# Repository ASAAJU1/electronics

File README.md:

Initial Conversion from the SVN Repo at:
http://code.google.com/p/jctc-electronics/

Most board and lbr files were made with eagle 5.x.
New designs will use Eagle 6.3 and up.

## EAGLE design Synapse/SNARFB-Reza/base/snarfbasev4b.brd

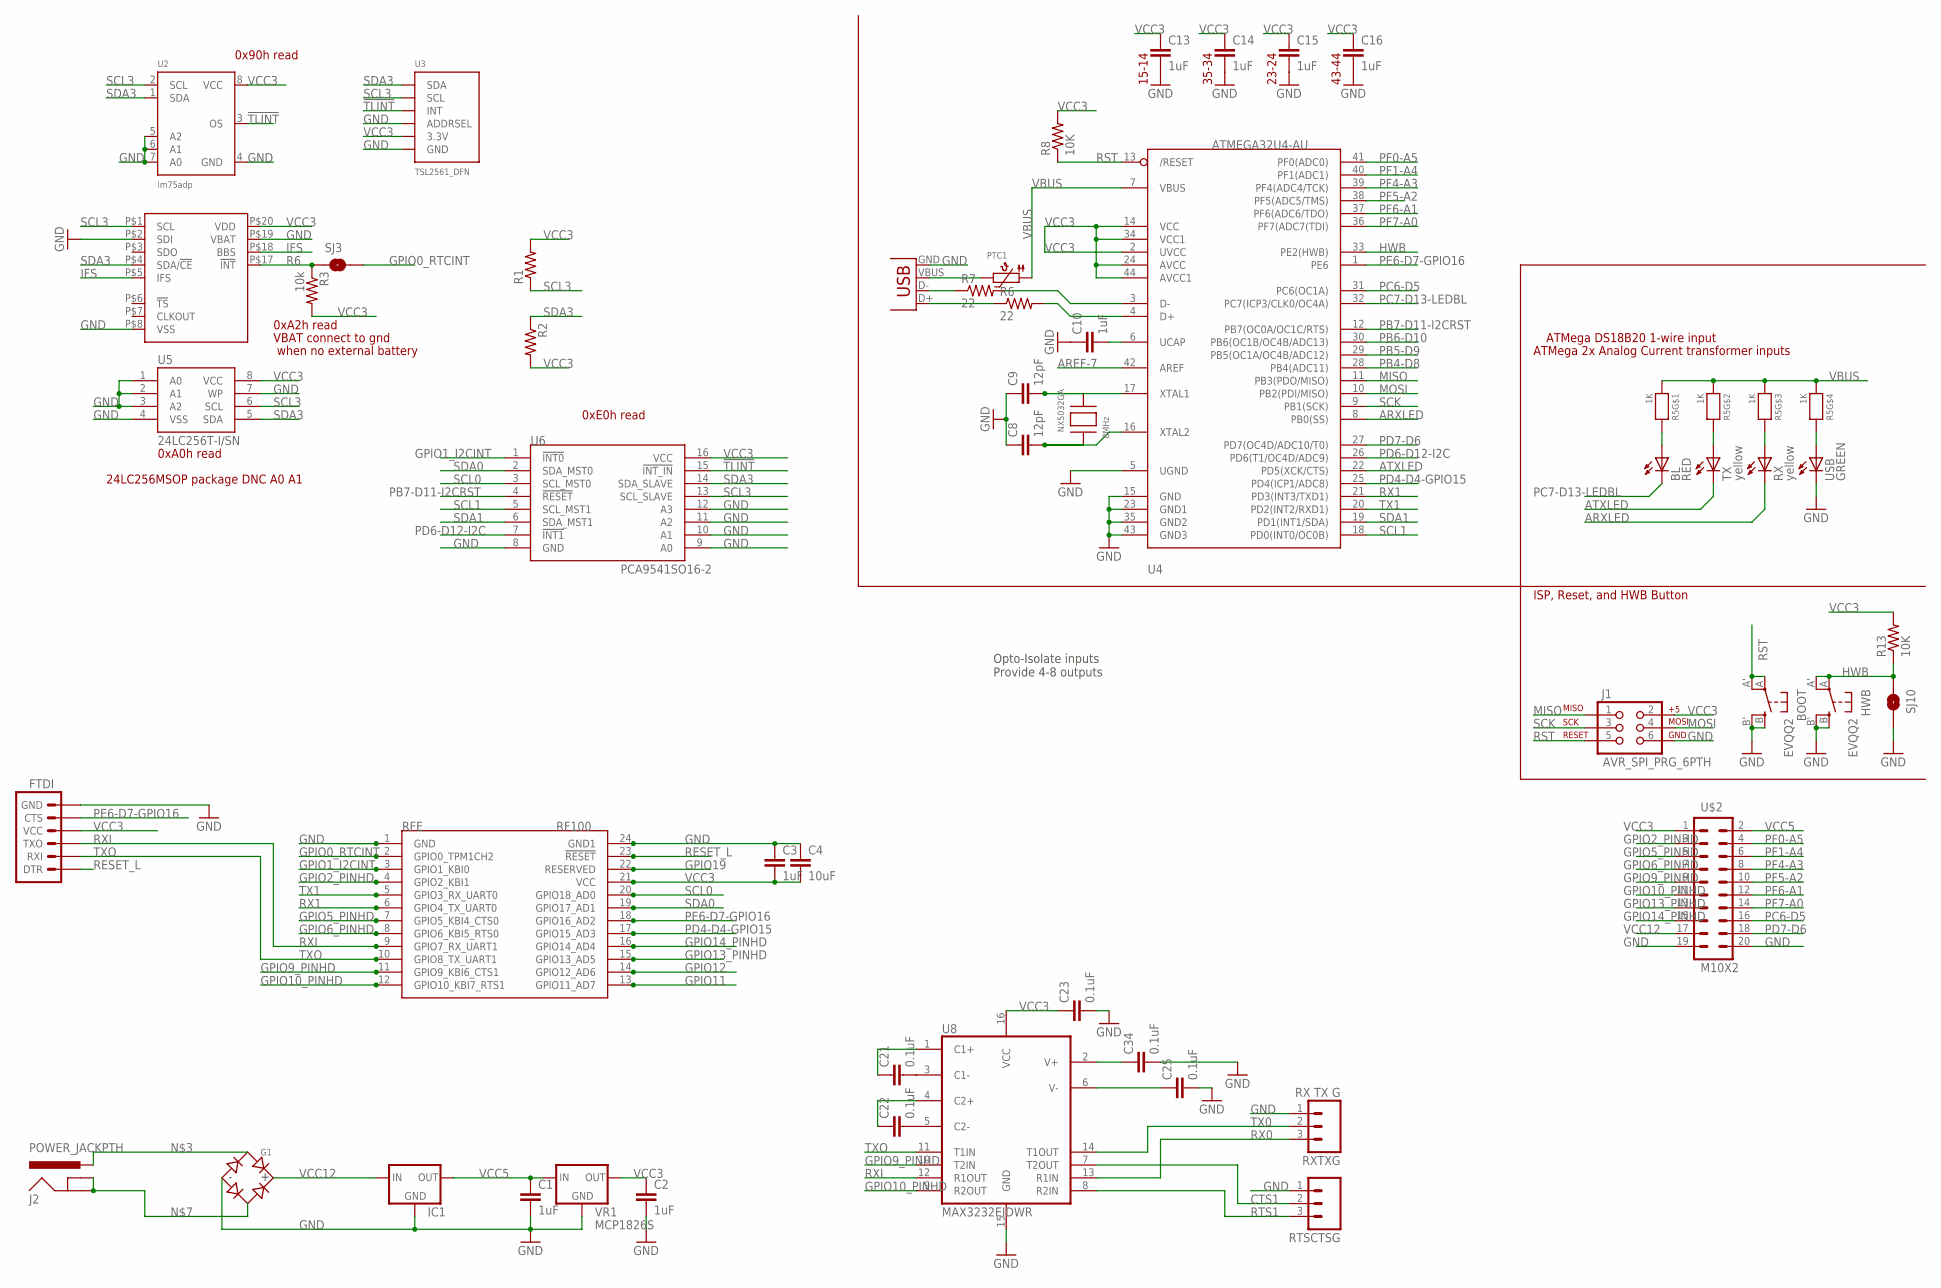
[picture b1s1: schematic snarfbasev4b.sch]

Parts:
BL: RED; LED-0603
BOOT: EVQQ2; EVQ-Q2
C1, C2, C3, C10, C13, C14, C15, C16: 1uF; 0805
C4: 10uF; 0805
C8, C9: 12pF; 0603-CAP
C21, C22, C23, C25, C34: 0.1uF; 0805
FTDI: ARDUINO_SERIAL_PROGRAMPTH; 1X06
G1: BRIDGERECTIFIER; SOIC-4
HWB: EVQQ2; EVQ-Q2
IC1: V_REG_78XXMURATA; TO220-MURATA
J1: AVR_SPI_PRG_6PTH; 2X3
J2: POWER_JACKPTH; POWER_JACK_PTH
NX5032GA: 8MHz; NX5032
PTC1: PTC1206; 1206
R1, R2: RESISTOR0805-RES; 0805
R3: 10k; 0805
R5: 1K; RESPACK_4X0603
R6, R7: 22; 0603-RES
R8, R13: 10K; 0805
RFE: RFE; SYNAPSERFENGINE-THM-SMT-JACK2
RTSCTSG: M03PTH; 1X03
RX: yellow; LED-0603
RXTXG: RX TX G; 1X03
SJ3: SOLDERJUMPERNC2; SJ_2S-NOTRACE
SJ10: HWB; SJ_2S-NO
TX: yellow; LED-0603
U1: PCF2129ASO20; SO20W
U2: lm75adp; TSSOP8
U3: TSL2561_DFN; TSL2561_FN
U4: ATMEGA32U4-AU; TQFP44
U5: 24LC256T-I/SN; SO08
U6: PCA9541SO16-2; SOIC16
U8: MAX3232EIDWR; SO016
U$2: M10X2; 2X10
USB: GREEN; LED-0603
VR1: MCP1826S; SOT223
X1: USBSMD; USB-MINIB

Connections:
!TLINT: U2.3 (OS), U3.INT, U6.15 (!INT_IN)
AREF-7: U4.42 (AREF)
ARXLED: RX.C, U4.8 (PB0(SS))
ATXLED: TX.C, U4.22 (PD5(XCK/CTS))
CTS1: RTSCTSG.2, U8.7 (T2OUT)
GND: BOOT.B (S), BOOT.B' (S1), C1.2, C2.2, C3.1, C4.1, C8.1, C9.1, C10.1, C13.2, C14.2, C15.2, C16.2, C23.2, C25.2, C34.2, FTDI.6 (GND), G1.-, HWB.B (S), HWB.B' (S1), IC1.GND, J1.6, RFE.1 (GND), RFE.24 (GND1), RFE.P1, RFE.P24, RFE.P201, RFE.P224, RTSCTSG.1, RXTXG.1, SJ10.2, U1.P$2 (SDI), U1.P$8 (VSS), U1.P$19 (VBAT), U2.4 (GND), U2.5 (A2), U2.6 (A1), U2.7 (A0), U3.ADR (ADDRSEL), U3.VSS (GND), U4.5 (UGND), U4.15 (GND), U4.23 (GND1), U4.35 (GND2), U4.43 (GND3), U5.1 (A0), U5.2 (A1), U5.3 (A2), U5.4 (VSS), U5.7 (WP), U6.8 (GND), U6.9 (A0), U6.10 (A1), U6.11 (A2), U6.12 (A3), U8.15 (GND), U$2.19, U$2.20, USB.C, VR1.2 (GND), VR1.4 (GND), X1.GND
GPIO0_RTCINT: RFE.2 (GPIO0_TPM1CH2), RFE.P2, RFE.P202, SJ3.2
GPIO1_I2CINT: RFE.3 (GPIO1_KBI0), RFE.P3, RFE.P203, U6.1 (!INT0)
GPIO2_PINHD: RFE.4 (GPIO2_KBI1), RFE.P4, RFE.P204, U$2.3
GPIO5_PINHD: RFE.7 (GPIO5_KBI4_CTS0), RFE.P7, RFE.P207, U$2.5
GPIO6_PINHD: RFE.8 (GPIO6_KBI5_RTS0), RFE.P8, RFE.P208, U$2.7
GPIO9_PINHD: RFE.11 (GPIO9_KBI6_CTS1), RFE.P11, RFE.P211, U8.10 (T2IN), U$2.9
GPIO10_PINHD: RFE.12 (GPIO10_KBI7_RTS1), RFE.P12, RFE.P212, U8.9 (R2OUT), U$2.11
GPIO11: RFE.13 (GPIO11_AD7), RFE.P13, RFE.P213
GPIO12: RFE.14 (GPIO12_AD6), RFE.P14, RFE.P214
GPIO13_PINHD: RFE.15 (GPIO13_AD5), RFE.P15, RFE.P215, U$2.13
GPIO14_PINHD: RFE.16 (GPIO14_AD4), RFE.P16, RFE.P216, U$2.15
GPIO19: RFE.22 (RESERVED), RFE.P22, RFE.P222
HWB: HWB.A, HWB.A' (P1), R13.1, SJ10.1, U4.33 (PE2(HWB))
IFS: U1.P$5 (IFS), U1.P$18 (BBS)
MISO: J1.1, U4.11 (PB3(PDO/MISO))
MOSI: J1.4, U4.10 (PB2(PDI/MISO))
unnamed: G1.~1 (AC1), J2.PWR
unnamed: C10.2, U4.6 (UCAP)
unnamed: BL.A, R5.8 (2)
unnamed: G1.~2 (AC2), J2.GND, J2.GNDBREAK
unnamed: R5.7 (2), TX.A
unnamed: R5.6 (2), RX.A
unnamed: R5.5 (2), USB.A
unnamed: C21.2, U8.3 (C1-)
unnamed: C22.2, U8.5 (C2-)
unnamed: C34.1, U8.2 (V+)
unnamed: C25.1, U8.6 (V-)
unnamed: C21.1, U8.1 (C1+)
unnamed: C22.1, U8.4 (C2+)
PB4-D8: U4.28 (PB4(ADC11))
PB5-D9: U4.29 (PB5(OC1A/OC4B/ADC12))
PB6-D10: U4.30 (PB6(OC1B/OC4B/ADC13))
PB7-D11-I2CRST: U4.12 (PB7(OC0A/OC1C/RTS)), U6.4 (!RESET)
PC6-D5: U4.31 (PC6(OC1A)), U$2.16
PC7-D13-LEDBL: BL.C, U4.32 (PC7(ICP3/CLK0/OC4A))
PD4-D4-GPIO15: RFE.17 (GPIO15_AD3), RFE.P17, RFE.P217, U4.25 (PD4(ICP1/ADC8))
PD6-D12-I2C: U4.26 (PD6(T1/OC4D/ADC9)), U6.7 (!INT1)
PD7-D6: U4.27 (PD7(OC4D/ADC10/T0)), U$2.18
PE6-D7-GPIO16: FTDI.5 (CTS), RFE.18 (GPIO16_AD2), RFE.P18, RFE.P218, U4.1 (PE6)
PF0-A5: U4.41 (PF0(ADC0)), U$2.4
PF1-A4: U4.40 (PF1(ADC1)), U$2.6
PF4-A3: U4.39 (PF4(ADC4/TCK)), U$2.8
PF5-A2: U4.38 (PF5(ADC5/TMS)), U$2.10
PF6-A1: U4.37 (PF6(ADC6/TDO)), U$2.12
PF7-A0: U4.36 (PF7(ADC7(TDI)), U$2.14
R6: R3.1, SJ3.1, U1.P$17 (!INT)
RESET_L: FTDI.1 (DTR), RFE.23 (!RESET), RFE.P23, RFE.P223
RST: BOOT.A, BOOT.A' (P1), J1.5, R8.1, U4.13 (/RESET)
RTS1: RTSCTSG.3, U8.8 (R2IN)
RX0: RXTXG.3, U8.13 (R1IN)
RX1: RFE.6 (GPIO4_TX_UART0), RFE.P6, RFE.P206, U4.21 (PD3(INT3/TXD1))
RXI: FTDI.3 (TXO), RFE.9 (GPIO7_RX_UART1), RFE.P9, RFE.P209, U8.12 (R1OUT)
SCK: J1.3, U4.9 (PB1(SCK))
SCL0: RFE.20 (GPIO18_AD0), RFE.P20, RFE.P220, U6.3 (SCL_MST0)
SCL1: U4.18 (PD0(INT0/OC0B)), U6.5 (SCL_MST1)
SCL3: R1.1, U1.P$1 (SCL), U2.2 (SCL), U3.CLK (SCL), U5.6 (SCL), U6.13 (SCL_SLAVE)
SDA0: RFE.19 (GPIO17_AD1), RFE.P19, RFE.P219, U6.2 (SDA_MST0)
SDA1: U4.19 (PD1(INT1/SDA)), U6.6 (SDA_MST1)
SDA3: R2.1, U1.P$4 (SDA/!CE), U2.1 (SDA), U3.DATA (SDA), U5.5 (SDA), U6.14 (SDA_SLAVE)
TX0: RXTXG.2, U8.14 (T1OUT)
TX1: RFE.5 (GPIO3_RX_UART0), RFE.P5, RFE.P205, U4.20 (PD2(INT2/RXD1))
TXO: FTDI.2 (RXI), RFE.10 (GPIO8_TX_UART1), RFE.P10, RFE.P210, U8.11 (T1IN)
UDM_N: R7.1, X1.D-
UDM_P: R6.1, X1.D+
UD_N: R7.2, U4.3 (D-)
UD_P: R6.2, U4.4 (D+)
VBUS: PTC1.1, R5.1, R5.2 (1), R5.3 (1), R5.4 (1), U4.7 (VBUS)
VBUSRAW: PTC1.2, X1.VBUS
VCC3: C2.1, C3.2, C4.2, C13.1, C14.1, C15.1, C16.1, C23.1, FTDI.4 (VCC), J1.2, R1.2, R2.2, R3.2, R8.2, R13.2, RFE.21 (VCC), RFE.P21, RFE.P221, U1.P$20 (VDD), U2.8 (VCC), U3.VDD (3.3V), U4.2 (UVCC), U4.14 (VCC), U4.24 (AVCC), U4.34 (VCC1), U4.44 (AVCC1), U5.8 (VCC), U6.16 (VCC), U8.16 (VCC), U$2.1, VR1.3 (OUT)
VCC5: C1.1, IC1.OUT, U$2.2, VR1.1 (IN)
VCC12: G1.+, IC1.IN, U$2.17
XTAL_N: C9.2, NX5032GA.P$2, U4.17 (XTAL1)
XTAL_P: C8.2, NX5032GA.P$1, U4.16 (XTAL2)

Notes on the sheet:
24LC256MSOP package DNC A0 A1
0xA2h read
0xA0h read
0x90h read
VBAT connect to gnd
when no external battery
43-44
35-34
23-24
15-14
Opto-Isolate inputs Provide 4-8 outputs
ISP, Reset, and HWB Button
ATMega DS18B20 1-wire input
ATMega 2x Analog Current transformer inputs
0xE0h read

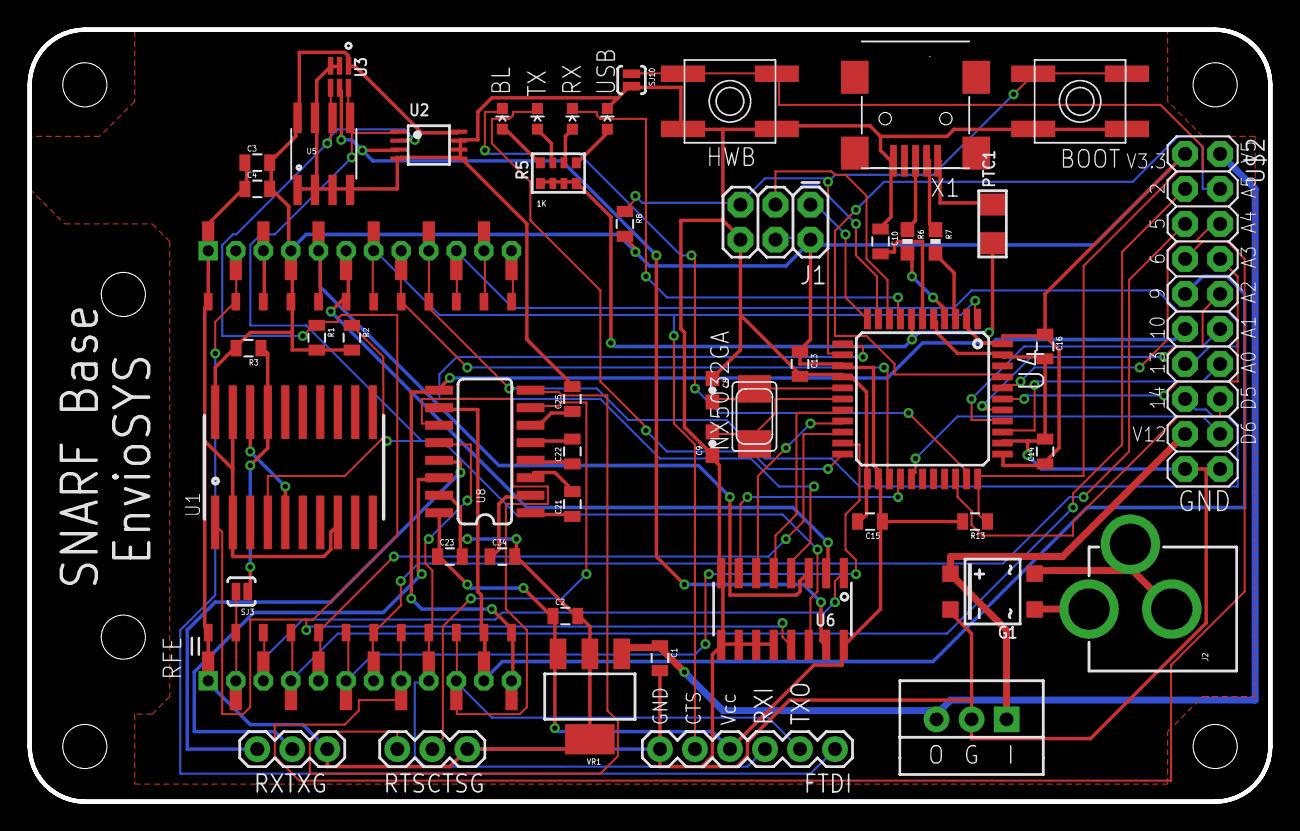
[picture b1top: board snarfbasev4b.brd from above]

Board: 2 copper layers, 90.0 x 56.0 mm, 54 parts (1 on the bottom side), 75 nets.

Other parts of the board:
U$1: ENVIOSYS_LOGO2
U$3: DP9056_V1

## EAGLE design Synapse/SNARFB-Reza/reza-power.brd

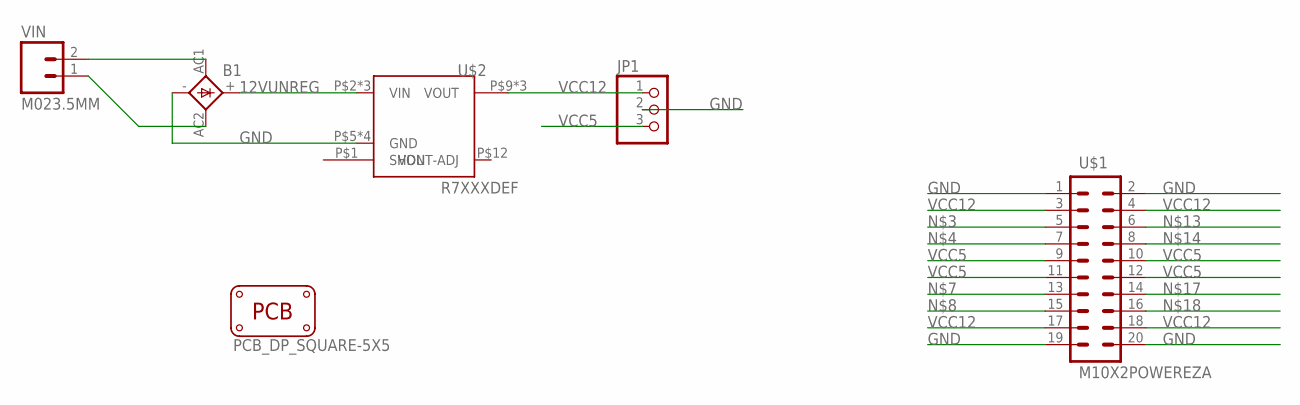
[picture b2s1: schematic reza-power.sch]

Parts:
B1: 1KAB
JP1: PINHD-1X3CB; 1X03-CLEANBIG
PCB1: PCB_DP_SQUARE-5X5; DP5050_V1
U$1: M10X2POWEREZA; REZAPOWER_INTERBOARD
U$2: R7XXXDEF; 1X12_RECOM
VIN: M023.5MM; SCREWTERMINAL-3.5MM-2

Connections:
12VUNREG: B1.+, U$2.P$2 (VIN), U$2.P$3 (VIN), U$2.P$4 (VIN)
24VAC1: B1.AC2, VIN.1
24VAC2: B1.AC1, VIN.2
GND: B1.-, JP1.2, U$1.1, U$1.2, U$1.19, U$1.20, U$2.P$5 (GND), U$2.P$6 (GND), U$2.P$7 (GND), U$2.P$8 (GND)
VCC5: JP1.3, U$1.9, U$1.10, U$1.11, U$1.12
VCC12: JP1.1, U$1.3, U$1.4, U$1.17, U$1.18, U$2.P$9 (VOUT), U$2.P$10 (VOUT), U$2.P$11 (VOUT)

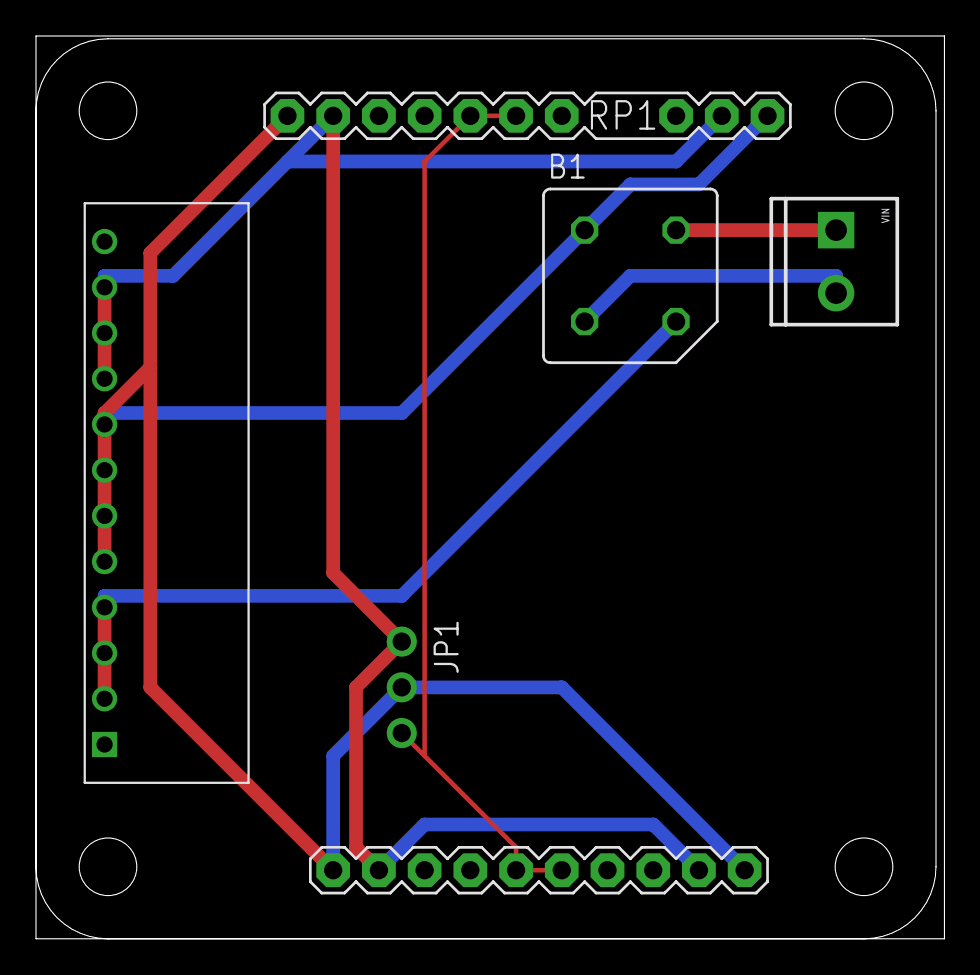
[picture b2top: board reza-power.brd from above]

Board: 2 copper layers, 50.5 x 50.2 mm, 6 parts (0 on the bottom side), 6 nets.

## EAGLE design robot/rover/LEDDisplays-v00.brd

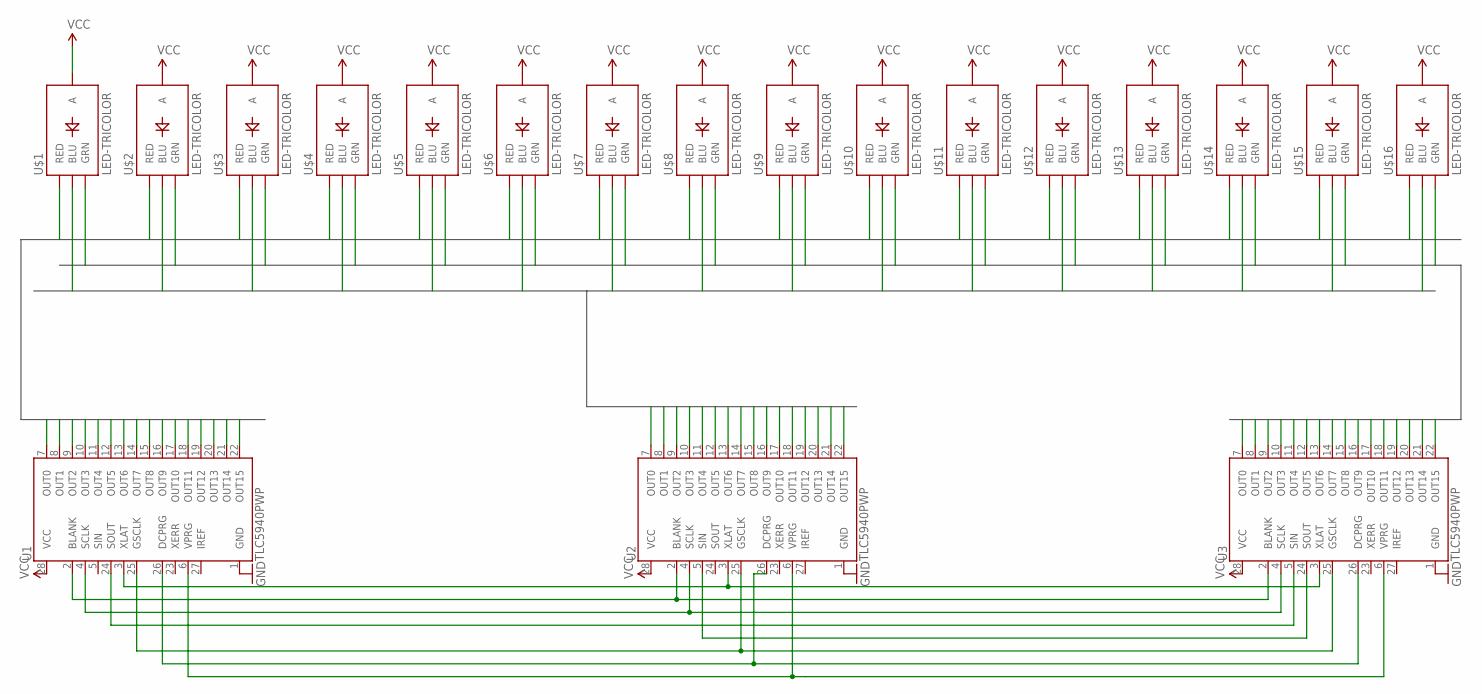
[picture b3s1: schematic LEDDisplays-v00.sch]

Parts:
U1, U2, U3: TLC5940PWP; TSSOP28-GROUNDPAD
U$1, U$2, U$3, U$4, U$5, U$6, U$7, U$8, U$9, U$10, U$11, U$12, U$13, U$14, U$15, U$16: LED-TRICOLOR; LED-TRICOLOR-SMD

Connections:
B1: U2.7 (OUT0), U$1.B (BLU)
B2: U2.8 (OUT1), U$2.B (BLU)
B3: U2.9 (OUT2), U$3.B (BLU)
B4: U2.10 (OUT3), U$4.B (BLU)
B5: U2.11 (OUT4), U$5.B (BLU)
B6: U2.12 (OUT5), U$6.B (BLU)
B7: U2.13 (OUT6), U$7.B (BLU)
B8: U2.14 (OUT7), U$8.B (BLU)
B9: U2.15 (OUT8), U$9.B (BLU)
B10: U2.16 (OUT9), U$10.B (BLU)
B11: U2.17 (OUT10), U$11.B (BLU)
B12: U2.18 (OUT11), U$12.B (BLU)
B13: U2.19 (OUT12), U$13.B (BLU)
B14: U2.20 (OUT13), U$14.B (BLU)
B15: U2.21 (OUT14), U$15.B (BLU)
B16: U2.22 (OUT15), U$16.B (BLU)
BLANK: U1.2 (BLANK), U2.2 (BLANK), U3.2 (BLANK)
DCPRG: U1.26 (DCPRG), U2.26 (DCPRG), U3.26 (DCPRG)
G1: U3.7 (OUT0), U$1.G (GRN)
G2: U3.8 (OUT1), U$2.G (GRN)
G3: U3.9 (OUT2), U$3.G (GRN)
G4: U3.10 (OUT3), U$4.G (GRN)
G5: U3.11 (OUT4), U$5.G (GRN)
G6: U3.12 (OUT5), U$6.G (GRN)
G7: U3.13 (OUT6), U$7.G (GRN)
G8: U3.14 (OUT7), U$8.G (GRN)
G9: U3.15 (OUT8), U$9.G (GRN)
G10: U3.16 (OUT9), U$10.G (GRN)
G11: U3.17 (OUT10), U$11.G (GRN)
G12: U3.18 (OUT11), U$12.G (GRN)
G13: U3.19 (OUT12), U$13.G (GRN)
G14: U3.20 (OUT13), U$14.G (GRN)
G15: U3.21 (OUT14), U$15.G (GRN)
G16: U3.22 (OUT15), U$16.G (GRN)
GND: U1.1 (GND), U2.1 (GND), U3.1 (GND)
GSCLK: U1.25 (GSCLK), U2.25 (GSCLK), U3.25 (GSCLK)
unnamed: U1.24 (SOUT), U3.5 (SIN)
unnamed: U2.5 (SIN), U3.24 (SOUT)
R1: U1.7 (OUT0), U$1.R (RED)
R2: U1.8 (OUT1), U$2.R (RED)
R3: U1.9 (OUT2), U$3.R (RED)
R4: U1.10 (OUT3), U$4.R (RED)
R5: U1.11 (OUT4), U$5.R (RED)
R6: U1.12 (OUT5), U$6.R (RED)
R7: U1.13 (OUT6), U$7.R (RED)
R8: U1.14 (OUT7), U$8.R (RED)
R9: U1.15 (OUT8), U$9.R (RED)
R10: U1.16 (OUT9), U$10.R (RED)
R11: U1.17 (OUT10), U$11.R (RED)
R12: U1.18 (OUT11), U$12.R (RED)
R13: U1.19 (OUT12), U$13.R (RED)
R14: U1.20 (OUT13), U$14.R (RED)
R15: U1.21 (OUT14), U$15.R (RED)
R16: U1.22 (OUT15), U$16.R (RED)
SCLK: U1.4 (SCLK), U2.4 (SCLK), U3.4 (SCLK)
VCC: U1.28 (VCC), U2.28 (VCC), U3.28 (VCC), U$1.A, U$2.A, U$3.A, U$4.A, U$5.A, U$6.A, U$7.A, U$8.A, U$9.A, U$10.A, U$11.A, U$12.A, U$13.A, U$14.A, U$15.A, U$16.A
VPRG: U1.6 (VPRG), U2.6 (VPRG), U3.6 (VPRG)
XLAT: U1.3 (XLAT), U2.3 (XLAT), U3.3 (XLAT)

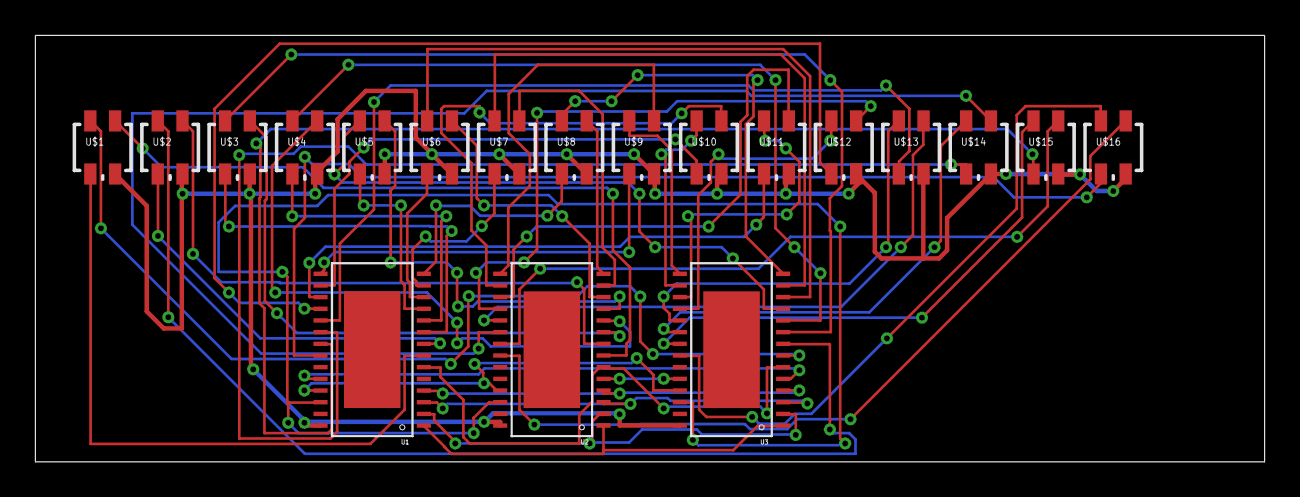
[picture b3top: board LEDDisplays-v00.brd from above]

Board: 2 copper layers, 69.5 x 24.1 mm, 19 parts (0 on the bottom side), 58 nets.

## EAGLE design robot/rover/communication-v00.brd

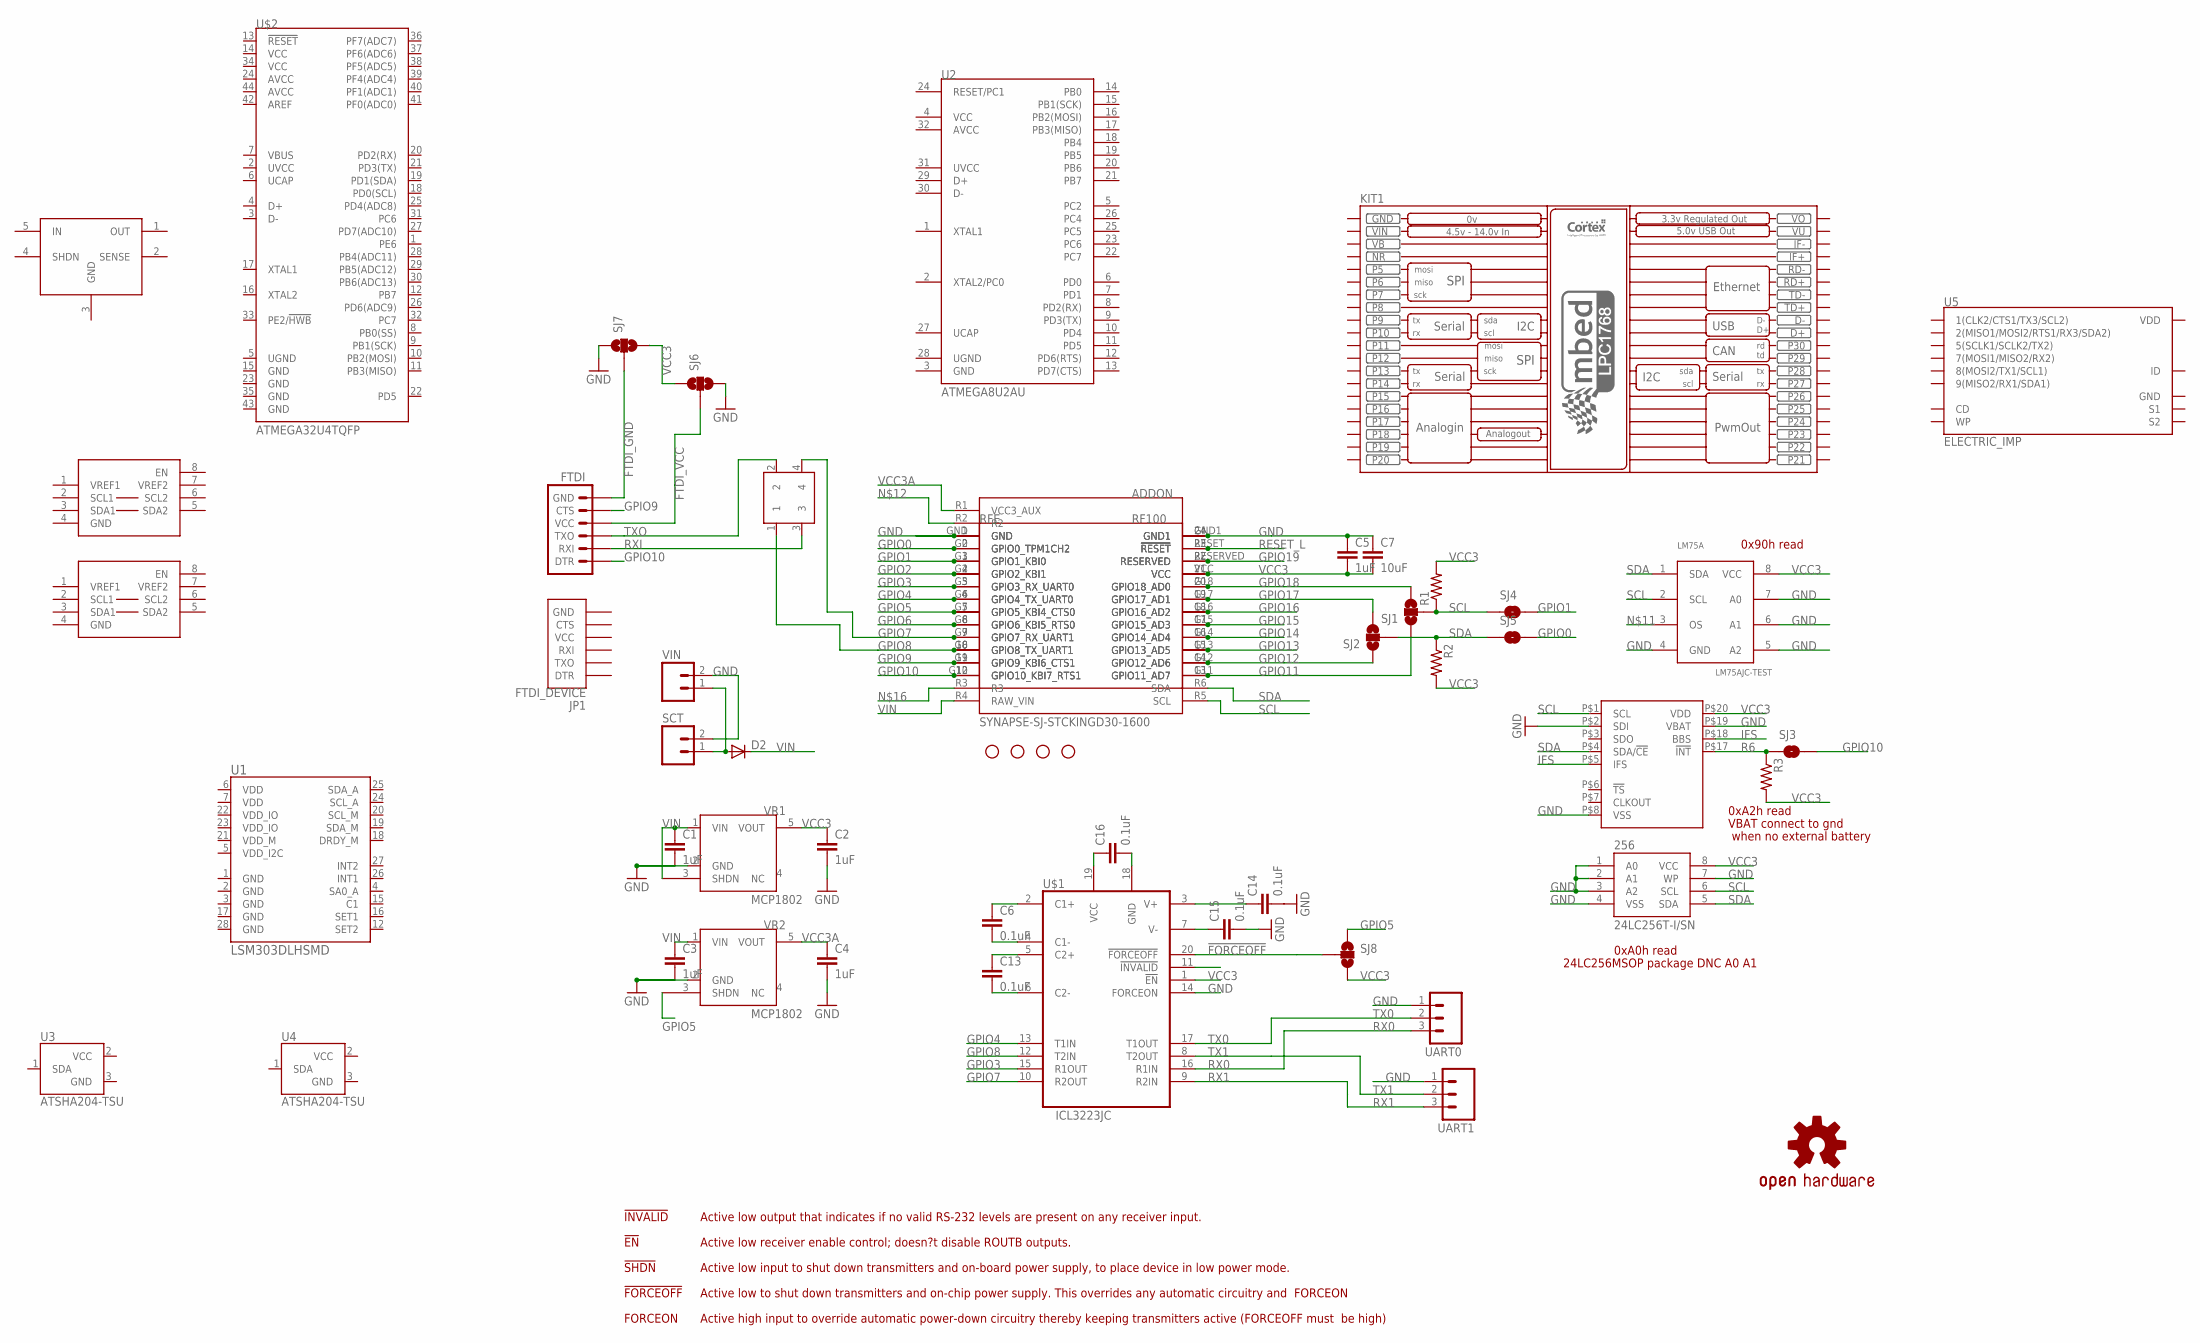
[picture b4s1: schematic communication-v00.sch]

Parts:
256: 24LC256T-I/SN; SO08
ADDON: SYNAPSE-SJ-STCKINGD30-1600; SYNSJ-STACK
C1, C2, C3, C4, C5: 1uF; 0805
C6, C13, C14, C15, C16: 0.1uF; 0805
C7: 10uF; 0805
D2: DIODESMA; SMA-DIODE
FTDI: ARDUINO_SERIAL_PROGRAMPTH; 1X06
JP1: FTDI_DEVICE; FTDI_DEVICE_SIDE
JP6, JP9, JP10, JP11: STAND-OFF
KIT1: MBED_NXP_LPC1768; MBED-KIT
LM75A: LM75AJC-TEST; TSSOP8-3MM
LOGO1: OSHW-LOGOL; OSHW-LOGO-L
PCF2129A: PCF2129ASO20; SO20W
R1, R2, R3: RESISTOR; 0805
RFE: RFE; SYNAPSERFENGINE-THM-SMT-JACK2
RXTX: SERIAL_CROSSOVER; 2X02_PTH
SCT: M023.5MM; SCREWTERMINAL-3.5MM-2
SJ1, SJ2: SOLDERJUMPER_2WAYS; SJ_3
SJ3: SOLDERJUMPERNC2; SJ_2S-NOTRACE
SJ4, SJ5: SOLDERJUMPERNO; SJ_2S-NO
SJ6, SJ7, SJ8: SOLDERJUMPER_2WAYPASTE1&2; SJ_3_PASTE1&2
U1: LSM303DLHSMD; LGA28-5X5
U2: ATMEGA8U2AU; TQFP32-08
U3, U4: ATSHA204-TSU; SOT23-3
U5: ELECTRIC_IMP; SD_MMC_SOCKET
U$1: ICL3223JC; TSSOP20-JC
U$2: ATMEGA32U4TQFP; SPARKFUN-DIGITALIC_TQFP44
U$3, U$4: PCA9306; PSOP-8
U$5: LT1528; Q5-DD
UART0, UART1: M03PTH; 1X03
VIN: M02PTH; 1X02
VR1, VR2: MCP1802; SOT23-5

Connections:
!FORCEOFF: SJ8.2, U$1.20 (!FORCEOFF)
!INVALID: U$1.11 (!INVALID)
FTDI_GND: FTDI.6 (GND), SJ7.2
FTDI_VCC: FTDI.4 (VCC), SJ6.2
GND: 256.1 (A0), 256.2 (A1), 256.3 (A2), 256.4 (VSS), 256.7 (WP), ADDON.GND, ADDON.GND1, C1.2, C2.2, C3.2, C4.2, C5.1, C7.1, C14.2, C15.2, C16.2, KIT1.GND, LM75A.4 (GND), LM75A.5 (A2), LM75A.6 (A1), LM75A.7 (A0), PCF2129A.P$2 (SDI), PCF2129A.P$8 (VSS), PCF2129A.P$19 (VBAT), RFE.1 (GND), RFE.24 (GND1), RFE.P1, RFE.P24, RFE.P201, RFE.P224, SCT.2, SJ6.3, SJ7.1, U$1.14 (FORCEON), U$1.18 (GND), UART0.1, UART1.1, VIN.2, VR1.2 (GND), VR2.2 (GND)
GPIO0: ADDON.G0 (GPIO0_TPM1CH2), RFE.2 (GPIO0_TPM1CH2), RFE.P2, RFE.P202, SJ5.2
GPIO1: ADDON.G1 (GPIO1_KBI0), RFE.3 (GPIO1_KBI0), RFE.P3, RFE.P203, SJ4.2
GPIO2: ADDON.G2 (GPIO2_KBI1), RFE.4 (GPIO2_KBI1), RFE.P4, RFE.P204
GPIO3: ADDON.G3 (GPIO3_RX_UART0), RFE.5 (GPIO3_RX_UART0), RFE.P5, RFE.P205, U$1.15 (R1OUT)
GPIO4: ADDON.G4 (GPIO4_TX_UART0), RFE.6 (GPIO4_TX_UART0), RFE.P6, RFE.P206, U$1.13 (T1IN)
GPIO5: ADDON.G5 (GPIO5_KBI4_CTS0), RFE.7 (GPIO5_KBI4_CTS0), RFE.P7, RFE.P207, SJ8.1, VR2.3 (SHDN)
GPIO6: ADDON.G6 (GPIO6_KBI5_RTS0), RFE.8 (GPIO6_KBI5_RTS0), RFE.P8, RFE.P208
GPIO7: ADDON.G7 (GPIO7_RX_UART1), RFE.9 (GPIO7_RX_UART1), RFE.P9, RFE.P209, RXTX.4, U$1.10 (R2OUT)
GPIO8: ADDON.G8 (GPIO8_TX_UART1), RFE.10 (GPIO8_TX_UART1), RFE.P10, RFE.P210, RXTX.1, U$1.12 (T2IN)
GPIO9: ADDON.G9 (GPIO9_KBI6_CTS1), FTDI.5 (CTS), RFE.11 (GPIO9_KBI6_CTS1), RFE.P11, RFE.P211
GPIO10: ADDON.G10 (GPIO10_KBI7_RTS1), FTDI.1 (DTR), RFE.12 (GPIO10_KBI7_RTS1), RFE.P12, RFE.P212, SJ3.2
GPIO11: ADDON.G11 (GPIO11_AD7), RFE.13 (GPIO11_AD7), RFE.P13, RFE.P213, SJ1.1
GPIO12: ADDON.G12 (GPIO12_AD6), RFE.14 (GPIO12_AD6), RFE.P14, RFE.P214, SJ2.1
GPIO13: ADDON.G13 (GPIO13_AD5), RFE.15 (GPIO13_AD5), RFE.P15, RFE.P215
GPIO14: ADDON.G14 (GPIO14_AD4), RFE.16 (GPIO14_AD4), RFE.P16, RFE.P216
GPIO15: ADDON.G15 (GPIO15_AD3), RFE.17 (GPIO15_AD3), RFE.P17, RFE.P217
GPIO16: ADDON.G16 (GPIO16_AD2), RFE.18 (GPIO16_AD2), RFE.P18, RFE.P218
GPIO17: ADDON.G17 (GPIO17_AD1), RFE.19 (GPIO17_AD1), RFE.P19, RFE.P219, SJ2.3
GPIO18: ADDON.G18 (GPIO18_AD0), RFE.20 (GPIO18_AD0), RFE.P20, RFE.P220, SJ1.3
GPIO19: ADDON.RESERVED, RFE.22 (RESERVED), RFE.P22, RFE.P222
IFS: PCF2129A.P$5 (IFS), PCF2129A.P$18 (BBS)
unnamed: C13.1, U$1.5 (C2+)
unnamed: C13.2, U$1.6 (C2-)
unnamed: C6.1, U$1.2 (C1+)
unnamed: C6.2, U$1.4 (C1-)
unnamed: C14.1, U$1.3 (V+)
unnamed: C15.1, U$1.7 (V-)
NR: KIT1.NR
R6: PCF2129A.P$17 (!INT), R3.1, SJ3.1
RESET_L: ADDON.RESET (!RESET), RFE.23 (!RESET), RFE.P23, RFE.P223
RX0: U$1.16 (R1IN), UART0.3
RX1: U$1.9 (R2IN), UART1.3
RXI: FTDI.2 (RXI), RXTX.3
SCL: 256.6 (SCL), ADDON.R5 (SCL), LM75A.2 (SCL), PCF2129A.P$1 (SCL), R1.1, SJ1.2, SJ4.1
SDA: 256.5 (SDA), ADDON.R6 (SDA), LM75A.1 (SDA), PCF2129A.P$4 (SDA/!CE), R2.1, SJ2.2, SJ5.1
TX0: U$1.17 (T1OUT), UART0.2
TX1: U$1.8 (T2OUT), UART1.2
TXO: FTDI.3 (TXO), RXTX.2
VB: KIT1.VB
VCC3: 256.8 (VCC), ADDON.VCC, C2.1, C5.2, C7.2, C16.1, LM75A.8 (VCC), PCF2129A.P$20 (VDD), R1.2, R2.2, R3.2, RFE.21 (VCC), RFE.P21, RFE.P221, SJ6.1, SJ7.3, SJ8.3, U$1.1 (!EN), U$1.19 (VCC), VR1.5 (VOUT)
VCC3A: ADDON.R1 (VCC3_AUX), C4.1, VR2.5 (VOUT)
VIN: ADDON.R4 (RAW_VIN), C1.1, C3.1, D2.C, KIT1.VIN, VR1.1 (VIN), VR1.3 (SHDN), VR2.1 (VIN)
VIN_PREDIODE: D2.A, SCT.1, VIN.1
VO: KIT1.VOUT (VO)
VU: KIT1.VU

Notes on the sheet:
24LC256MSOP package DNC A0 A1
0xA2h read
0xA0h read
0x90h read
VBAT connect to gnd
when no external battery
Active low output that indicates if no valid RS-232 levels are present on any receiver input.
Active low receiver enable control; doesn?t disable ROUTB outputs.
Active low input to shut down transmitters and on-board power supply, to place device in low power mode.
Active low to shut down transmitters and on-chip power supply. This overrides any automatic circuitry and FORCEON
Active high input to override automatic power-down circuitry thereby keeping transmitters active (FORCEOFF must be high)
!INVALID
!EN
!SHDN
!FORCEOFF
FORCEON

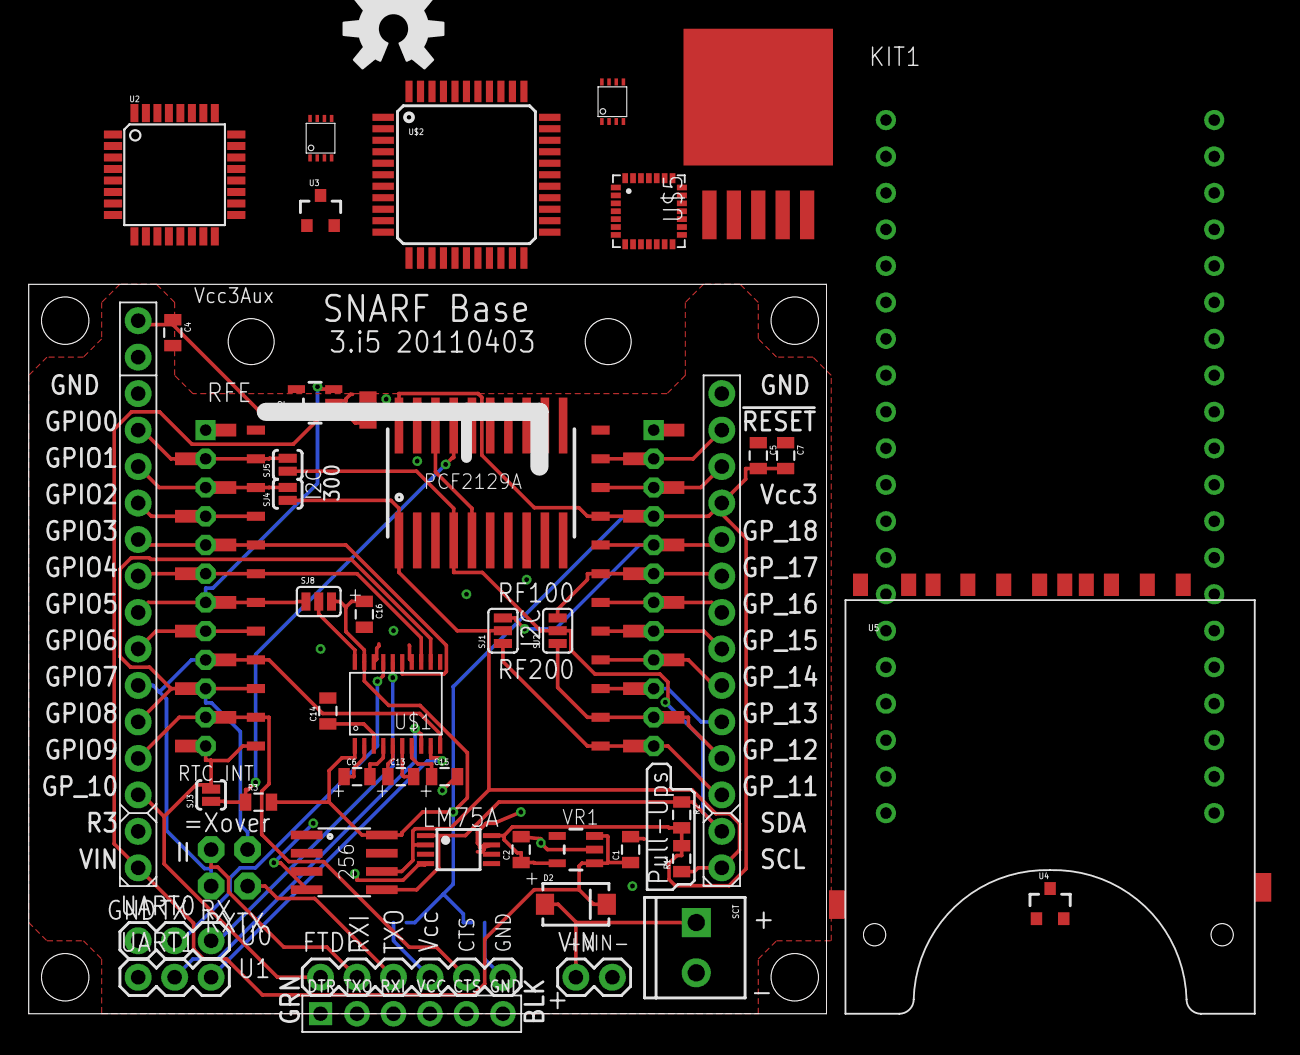
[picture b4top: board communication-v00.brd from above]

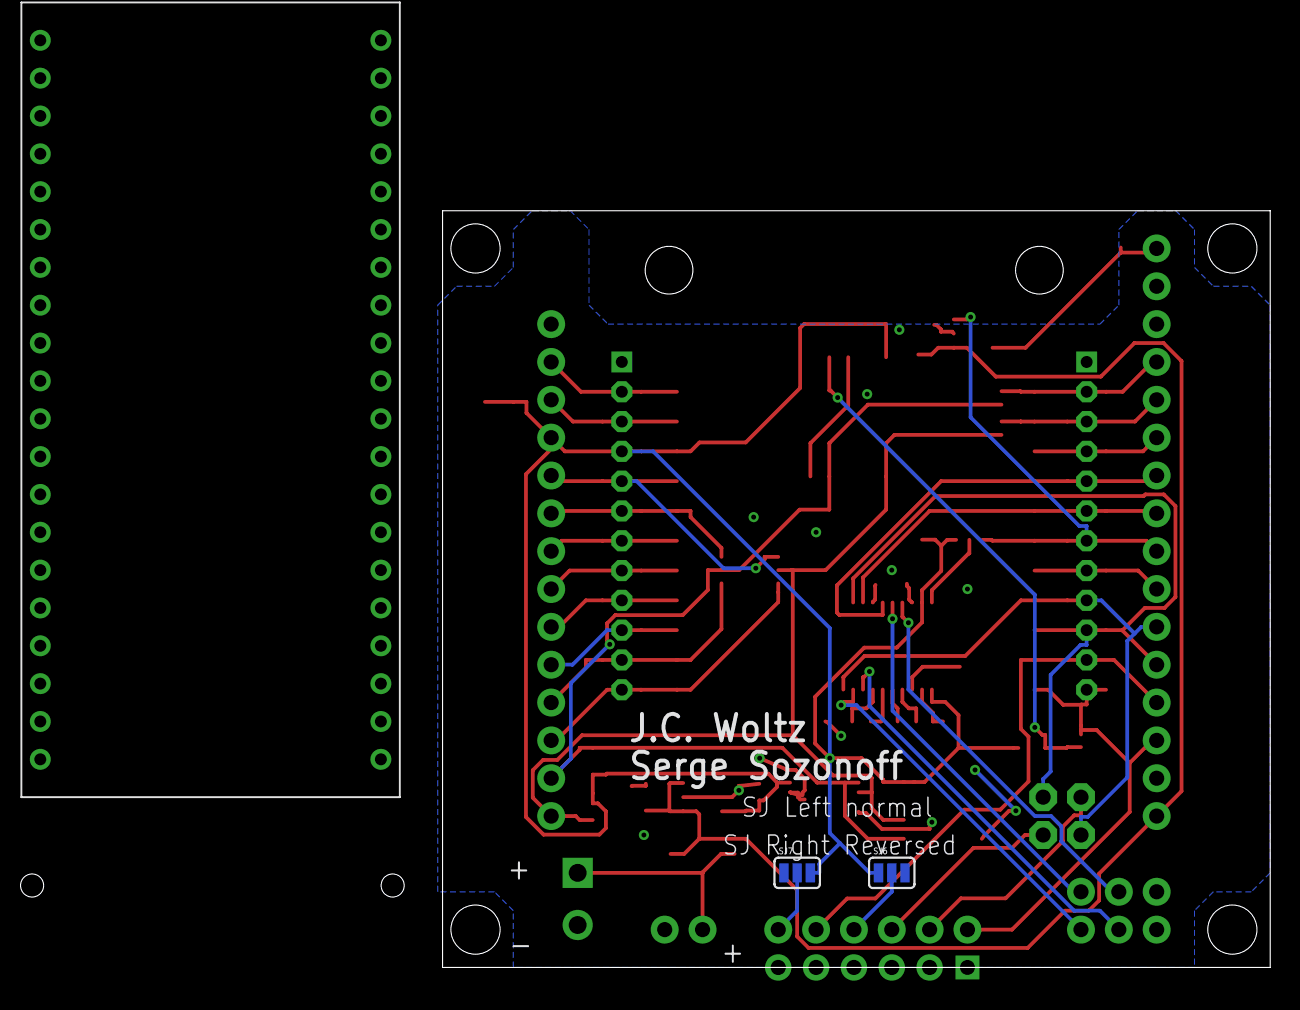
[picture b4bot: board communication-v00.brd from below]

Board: 2 copper layers, 55.5 x 50.8 mm, 53 parts (2 on the bottom side), 45 nets.

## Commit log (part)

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2010-11-17 renamed some methods
2010-11-17 Use ds2764_ss.py as a module Added rf_charger to test ds2764_ss.py as a module
2010-11-17 Charge status stuff is still screwed up
2010-11-20 Add portal and snappy code for pcf2129a. Modularized pcf2129a. Adding SB_test.py as my test. Based off of rf_charger from Serge.
2010-11-20 updated todo
2010-11-20 updated todo, v07-tmp-a2 is my everything board to see if everything will fit
2010-11-20 updated pcf2129a_m.py so that displayClockDT() will display 2 digits if any field is less that 10.
2010-11-22 slight component re-arrangement
2010-11-23 start lt3652-pre.sch
2010-11-26 adding SolarBase731-v00.brd
2010-11-26 continueing updates on SolarBase731-v00.brd
2010-11-28 adding rtc
2010-11-28 working on component placement to SolarBase731-v00.brd
2010-11-29 still working on component placement
2010-11-29 LTC schema updates
2010-11-29 SolarBase731-v00.brd component arrangement. start routing
2010-11-29 update some component values
2010-11-29 Added LEDS
2010-11-29 More parts updateing
2010-11-29 more docs and excel spreadsheet with maths
2010-11-30 adding atmega8u2 for usb/serial, and mcp73871 control
2010-11-30 Added proper inductor and diodes
2010-11-30 added some more components
2010-11-30 starting the pcb
2010-11-30 Add PCB case outline for the LP11p from Polycase started working on pcb layout for LTC3652
2010-11-30 updated and added some documentation for the LTC3652
2010-12-01 update jc libr
2010-12-01 Basic board
2010-12-01 deleting old sch file
2010-12-01 adding standoffs
2010-12-02 Routing .... routing and more routing attempts
2010-12-02 Take 1
2010-12-02 Turn up isolate on the polygon pour
2010-12-02 Fixing labels and other small details
2010-12-02 Done I guess..
2010-12-02 Not totally done yet :-)
2010-12-02 GND to GND attempt.... still not happy with this.
2010-12-03 Fixed the GND to BAT_GND connection
2010-12-03 Add a GND_AGND device
2010-12-03 Updated the LTC3652 package
2010-12-04 replacing components.
2010-12-04 fine tuning ;-)
2010-12-04 updating library. Updated brd to use jc_custom.lbr part. The parts have the tplace layer adjusted to avoid the tstop
2010-12-05 updated routing, generated gerbers
2010-12-05 archive
2010-12-05 Seperate the ground plane for PWR and "signalling" stuff
2010-12-05 More work on the round planes
2010-12-05 Version bump 0.1a
2010-12-05 generate gerbers, move to archive, increment
2010-12-05 update board version to 2
2010-12-05 provision for a 3 resistor network for Vfb
2010-12-05 trace adjustment
2010-12-06 generate lt3652-pre-v02-201012061428.zip gerbers. increment version numbers
2010-12-06 generated lt3652-pre-v03-201012061443.zip, increment version number
2010-12-07 change SOT23 diode package to SMA
2010-12-07 gerbs and version increase
2010-12-07 Added a generic SMC package type Diode
2010-12-07 These came back because of a conflict so I am deleting
2010-12-08 Added math for 3 resistor network for Vfb
2010-12-09 stuff
2010-12-11 adding sdcard
2010-12-11 First pass
2010-12-11 Autorouted .... better than me
2010-12-11 Better
2010-12-19 adding notes for arduino shield
2010-12-19 ArduinoShield-RFEngine-LLC-v00.brd now function and feature complete.
    TODO: place components
2010-12-29 ArduinoShield-RFEngine-LLC-v00.brd updating routing
2011-01-03 minor update
2011-01-05 minor updates and fixes to silkscreen and paste layer
2011-01-05 Adding initial start of xbee adapter
2011-01-05 xbeeRFsocket-v00.brd updates
2011-01-12 moved to other svn location
2011-01-22 Begin finalizing SNARF Base
2011-01-26 adding components still going through selection
2011-01-27 small naming updates
2011-01-31 small updates
2011-01-31 connected rs232
2011-02-03 Added ground pour to top. changed 24lc256 to msop8 package. Moved vregs
2011-02-04 start of routering
2011-02-04 updated routing, changed layers, now to start on silkscreen
2011-02-04 silkscreen
2011-02-04 silkscreening
2011-02-04 fixed some errors
2011-02-04 fixed trace clearance issues
2011-02-04 notes in sch
2011-02-04 vbat to gnd, updated notes in sch, updated prices in xls
2011-02-04 shrunk snarfbasebasics232-v03.sch to fit onto single page
2011-02-05 tied 24lc256 WP to VSS to enable writing. cannot be left floating
2011-02-05 LM75A was not connected to GND
2011-02-06 adding vcc/gnd crossover
2011-02-06 added pullup jumper for rtc int
2011-02-07 3h sent out to fab, future changes to 3i
2011-02-08 snarf-basecase-v00.brd testing
2011-02-08 minor updates to my lbr
2011-02-15 adding SysnapseWriless-BOB-v11g.brd
2011-02-19 working on microsd logging add on
2011-02-26 Adding snappy images to test the snarf-base board.
2011-03-06 updates to scripts. SNARF-BASE-testing.py now supports waking from RTC. pcf2129a_m.py modified to set INT on alarm
2011-03-19 updating snappy code and fixing some errors
2011-03-20 add SJ for UART0/UART1
2011-03-29 partial update of partslist
2011-04-02 start on 3rd version of AtMEGA32u4-uSD-AddON-v02.brd
2011-04-05 add comments
2011-04-16 adding script for steve
2011-04-26 updated some snappy scripts
2011-04-26 fix tab/space mixture
2011-05-03 Correct board outline
2011-05-14 turn off leds for power measurements
2011-05-14 update jc portal with synapse wx code for mcastcounter
2011-06-05 updated for rev 2 of pcb
2011-06-11 updating library
2011-06-17 Intermediate commit to catch snappy code up on all working computers. This may cause some breakage over the next few days.
2011-06-17 Begin a board for the SM200-BOB
2011-07-01 update snppy scripts: jc-portalrtc, m24lc256, pcf2129a
2011-07-04 adding non-eagle files for snarfbase-v03i5 board and sch
2011-07-07 updating atmega programming script and HEX File
2011-07-07 Initial check in of a datalogger using atmega32u4 and SM200 radio module
2011-08-20 Many updates to SNAPpy code
2011-08-20 updated jc-portalrtc in include the command and control on rpc request
2011-08-27 updates to snappy code
2011-09-02 Start a new revision of the SNARF-BOB
2011-09-02 Clean up directory for BOB
2011-10-09 unknown
2011-11-13 adding image of RTC BOB/PCF2129A/RTC-bob-brd.png
2011-12-26 Make changes to copy add portal scripts
2012-01-03 Update Portal/JC-Portal-simplified.py to remove modules. Copied code from modules into main script. Small updates to other snappy scripts
2012-01-07 updated year
2012-01-07 syn computers
2012-01-07 computer sync
2012-02-15 Add image of BOB 12i brd
2012-07-14 Trying to sync snappy files across computers
2012-07-14 Add contrib directory. update copy scripts.
2012-07-14 Fix broken XP snappy copy scripts
2012-07-14 first steps in mods for dir structure
2012-11-27 First git commit from svn fixing author info
2012-11-27 notes
2012-11-27 rover5start - initial commit
    Initial commit of rover5start
2012-12-02 LBR updated with eagle 6
    updated some descriptions, but no part changes
2012-12-08 adding mdeb libraries from mdeb site
2012-12-08 Adding various eagle libraries as submodules
2012-12-08 Adding basic eagle files used for dev
2012-12-08 Adding script to copy files to mac Eagle install
2012-12-09 Start robot files and and modified DRU
2012-12-09 Adding connections to RGB
2013-07-06 starting BBB
2013-12-17 temp stuff
2013-12-26 place holder
2013-12-30 comp sync
2013-12-31 prep for submission
2013-12-31 Adding PCA9541
2014-01-03 sync
2014-01-03 cleanup
2017-12-21 Added rudy.xml
2017-12-21 Added rudy 2
2017-12-21 Update rudy 2
2017-12-28 Added CCT MODEL.xml
2018-01-03 Added Untitled Diagram.xml
2018-01-10 Added TASK MODEL
2018-01-10 Update TASK MODEL

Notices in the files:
Synapse/SNARFB-Reza/base/snarfbasev4b.brd:
(c) Copyright 2013-2014 J.C. Woltz
parts and their libraries:
SparkFun-Connectors: Licensing: CC v3.0 Share-Alike You are welcome to use this library for commercial purposes.
microbuilder: This work is placed in the public domain, and may be freely used for commercial and non-commercial work with the following conditions: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
0_jc-custom-eagle6: CC BY-SA 3.0
